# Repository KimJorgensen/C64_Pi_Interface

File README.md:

# C64 - Pi Interface

Project is moved to https://codeberg.org/KimJorgensen/C64_Pi_Interface

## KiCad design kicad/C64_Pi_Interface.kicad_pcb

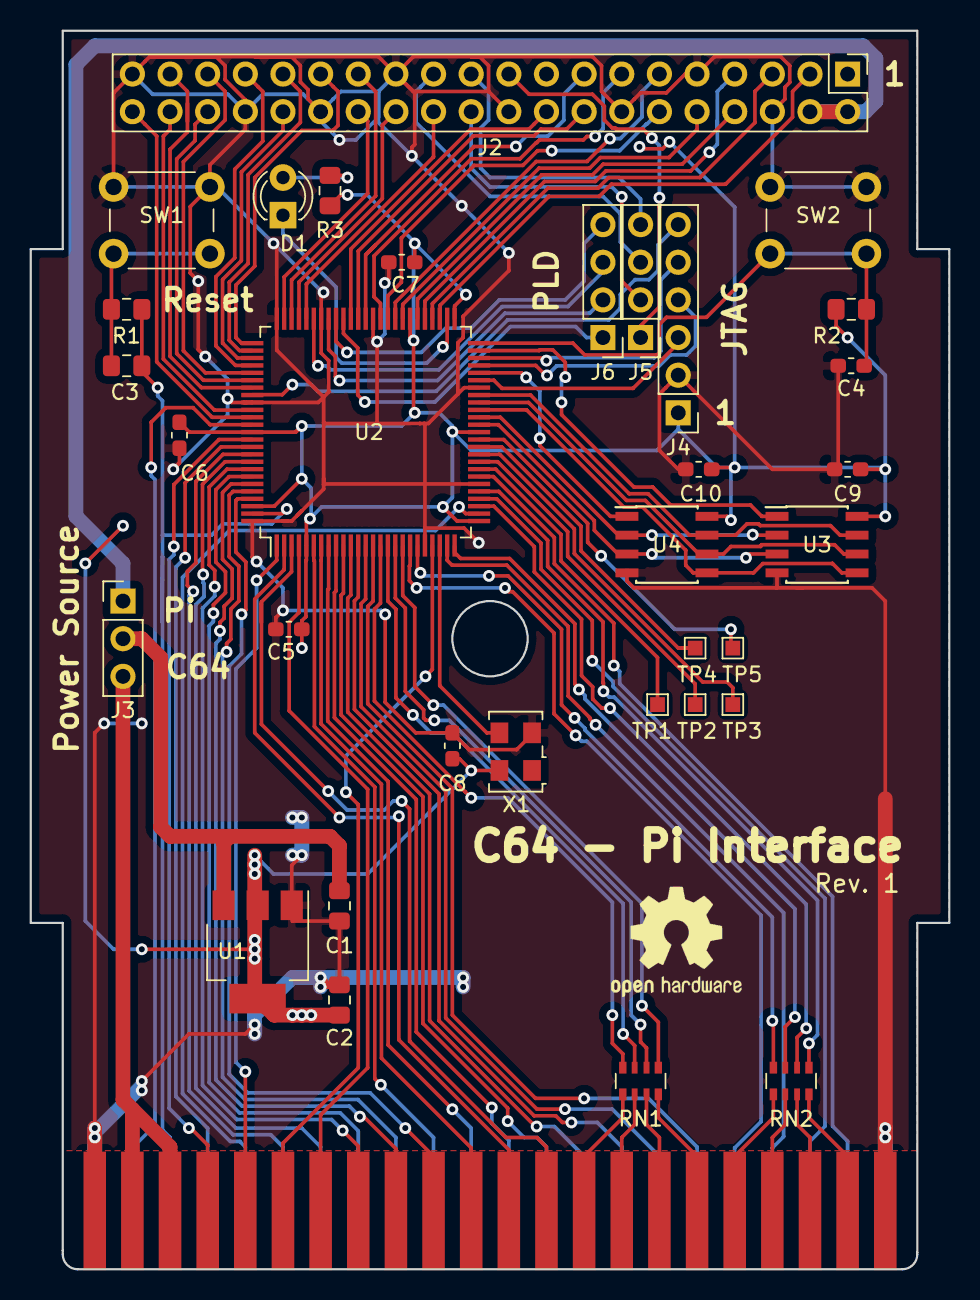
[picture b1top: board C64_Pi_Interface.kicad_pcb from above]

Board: 2 copper layers, 62.0 x 83.6 mm, 34 parts (0 on the bottom side), 104 nets.

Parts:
C1, C2, C3: 10u; C_0805_2012Metric_Pad1.15x1.40mm_HandSolder
C4, C5, C6, C7, C8, C9, C10: 100n; C_0603_1608Metric_Pad1.05x0.95mm_HandSolder
D1: LED; LED_D3.0mm
J1: C64-Exp-Port; C64-Cart
J2: Raspberry_Pi_2_3; PinHeader_2x20_P2.54mm_Vertical
J3: Power Source; PinHeader_1x03_P2.54mm_Vertical
J4: JTAG; PinHeader_1x06_P2.54mm_Vertical
J5: JTAG-PLD; PinHeader_1x04_P2.54mm_Vertical
J6: PLD; PinHeader_1x04_P2.54mm_Vertical
R1, R2: 10k; R_0805_2012Metric_Pad1.15x1.40mm_HandSolder
R3: 470R; R_0805_2012Metric_Pad1.15x1.40mm_HandSolder
RN1, RN2: 100R; R_Array_Convex_4x0603
SW1: Reset; SW_PUSH_6mm_H8mm
SW2: Switch; SW_PUSH_6mm_H8mm
TP1, TP2, TP3, TP4, TP5: TestPoint; TestPoint_Pad_1.0x1.0mm
U1: AMS1117-3.3; SOT-223-3_TabPin2
U2: XC95144XL-TQ100; TQFP-100_14x14mm_P0.5mm
U3: W25Q128FV; SOIC-8_3.9x4.9mm_P1.27mm
U4: 23LC1024; SOIC-8_3.9x4.9mm_P1.27mm
X1: 25MHz; Oscillator_SMD_EuroQuartz_XO53-4Pin_5.0x3.2mm

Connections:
+5C: J1.2, J1.3, J3.3
+5P: J2.2, J2.4, J3.1
+5V: C1.1, J3.2, U1.3
/A0: J1.Y, U2.32
/A1: J1.X, U2.29
/A2: J1.W, U2.24
/A3: J1.V, U2.19
/A4: J1.U, U2.14
/A5: J1.T, U2.13
/A6: J1.S, U2.12
/A7: J1.R, U2.11
/A8: J1.P, U2.10
/A9: J1.N, U2.9
/A10: J1.M, U2.8
/A11: J1.L, U2.6
/A12: J1.K, U2.96
/A13: J1.J, U2.94
/A14: J1.H, U2.92
/A15: J1.F, U2.91
/BA: J1.12, U2.2
/CD0: J1.21, RN2.4
/CD1: J1.20, RN2.3
/CD2: J1.19, RN2.2
/CD3: J1.18, RN2.1
/CD4: J1.17, RN1.4
/CD5: J1.16, RN1.3
/CD6: J1.15, RN1.2
/CD7: J1.14, RN1.1
/CLK: U2.23, X1.3
/D0: RN2.5, U2.30
/D1: RN2.6, U2.28
/D2: RN2.7, U2.25
/D3: RN2.8, U2.20
/D4: RN1.5, U2.18
/D5: RN1.6, U2.17
/D6: RN1.7, U2.16
/D7: RN1.8, U2.15
/D_CLK: J1.6, U2.22
/G0: J2.27, U2.73
/G1: J2.28, U2.74
/G2: J2.3, U2.53
/G3: J2.5, U2.54
/G4: J2.7, U2.55
/G5: J2.29, U2.76
/G6: J2.31, U2.77
/G7: J2.26, U2.72
/G8: J2.24, U2.71
/G9: J6.4, U2.67
/G10: J6.1, U2.66
/G11: J6.3, U2.70
/G12: J2.32, U2.78
/G13: J2.33, U2.79
/G14: J2.8, U2.56
/G15: J2.10, U2.58
/G16: J2.36, U2.81
/G17: J2.11, U2.59
/G18: J2.12, U2.60
/G19: J2.35, U2.80
/G20: J2.38, U2.85
/G21: J2.40, U2.86
/G22: J2.15, U2.63
/G23: J2.16, U2.64
/G24: J2.18, U2.65
/G25: J6.2, U2.68
/G26: J2.37, U2.82
/G27: J2.13, U2.61
/JG9: J2.21, J5.4
/JG10: J2.19, J5.1
/JG11: J2.23, J5.3
/JG25: J2.22, J5.2
/MISO: U2.40, U3.2, U4.2
/MOSI: U2.41, U3.5, U4.5
/PHI2: J1.E, U2.27
/R~W: J1.5, U2.1
/SCK: U2.42, U3.6, U4.6
/TCK: J4.5, U2.48
/TDI: J4.3, U2.45
/TDO: J4.6, U2.83
/TMS: J4.4, U2.47
/TP1: TP1.1, U2.33
/TP2: TP2.1, U2.34
/TP3: TP3.1, U2.35
/TP4: TP4.1, U2.36
/TP5: TP5.1, U2.37
/~DMA: J1.13, U2.3
/~EXROM: J1.9, U2.95
/~FLASH_CS: U2.49, U3.1
/~GAME: J1.8, U2.93
/~HOLD: U2.43, U3.7, U4.7
/~IO1: J1.7, U2.4
/~IO2: J1.10, U2.97
/~IRQ: J1.4, U2.89
/~LED: D1.1, U2.52
/~NMI: J1.D, U2.90
/~RAM_CS: U2.46, U4.1
/~RESET: C3.1, J1.C, R1.1, U2.99
/~ROMH: J1.B, U2.87
/~ROML: J1.11, U2.7
/~SW2: C4.2, R2.2, SW2.1, U2.50
/~WP: U2.39, U3.3, U4.3
GND: C1.2, C2.2, C4.1, C5.2, C6.2, C7.2, C8.2, C9.2, C10.2, J1.1, J1.22, J1.A, J1.Z, J2.6, J2.9, J2.14, J2.20, J2.25, J2.30, J2.34, J2.39, J4.2, SW1.1, SW2.2, U1.1, U2.21, U2.31, U2.44, U2.62, U2.69, U2.75, U2.84, U2.100, U3.4, U4.4, X1.2
unnamed: C3.2, R1.2, SW1.2
unnamed: D1.2, R3.2
VCC: C2.1, C5.1, C6.1, C7.1, C8.1, C9.1, C10.1, J4.1, R2.1, R3.1, U1.2, U2.5, U2.26, U2.38, U2.51, U2.57, U2.88, U2.98, U3.8, U4.8, X1.4

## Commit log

2019-07-13 First version
2025-12-18 Move to Codeberg
